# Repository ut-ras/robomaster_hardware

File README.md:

# Onboarding test branch

Use this branch to get accustomed to the git & github workflow, the current files are just a copy of the turret branch.

**Use `git clone  --recursive [Repository URL]` to clone our hardware repo**, as not doing so will not copy the files needed from the [RAS KiCAD Library](https://github.com/ut-ras/KiCad_Library.git)

It will put you on the `main` branch first, use `git switch onboard` to switch to this onboard branch.

To get the URL for this onboarding branch use the green `<> Code` button and copy the URL.

To confirm you are done with onboarding, clone this branch, edit this markdown file according to the directions below, and stage/commit/push the changes to this github repo:

Type your name and GitHub username here:

- Morris Lin : MorrisYLin
- Egan Wang:0 BaRho80
- Andrew Nguyen : AndrewNguy
- Sanjana Kishore : jujube6363
- Raeesa Karim : RaeesaKarim
- Nithin Reddy : NReddy101
- Sarthak Sarans : SarthakSarans

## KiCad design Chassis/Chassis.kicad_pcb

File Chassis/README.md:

# Chassis board

This project contains the chassis board, which routes power and CAN to the wheels from the PMM and the Dev Board, respectively.  
Also, a buck converter that drives the 19V power needed for the CV board. This is sent up the slip ring.

> _NOTE: 3D models will not work until someone figures out a clean way to use relative URLs for 3D models_

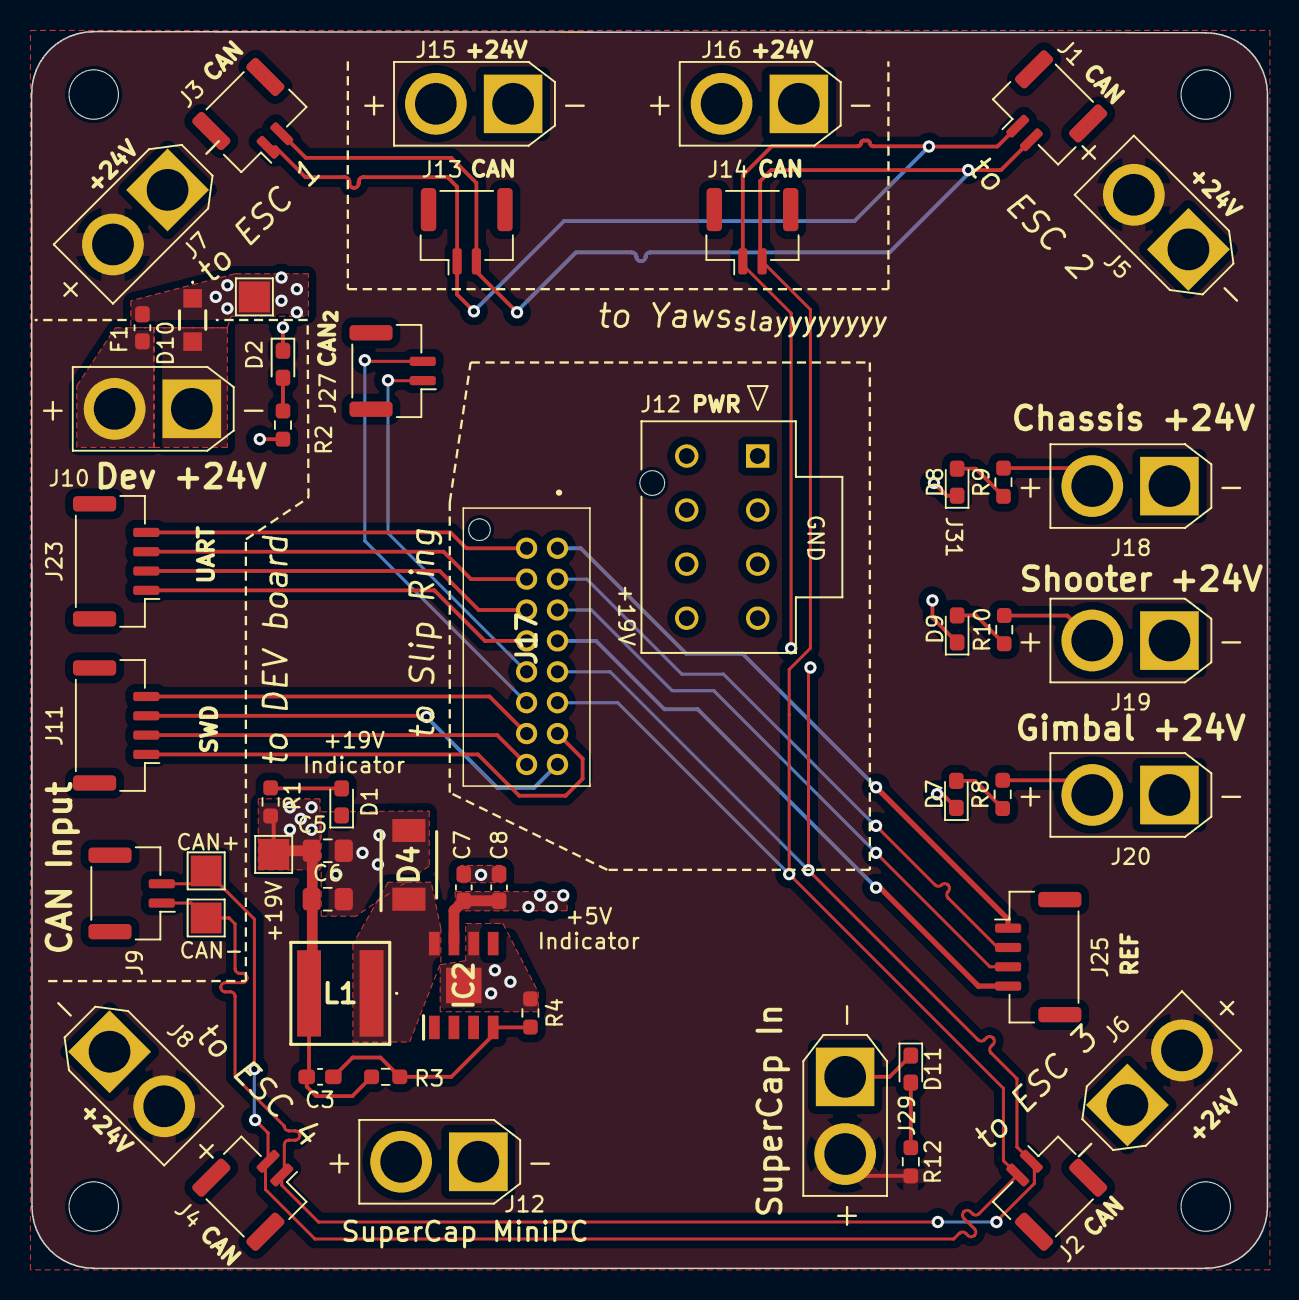
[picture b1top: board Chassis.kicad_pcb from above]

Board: 4 copper layers, 80.0 x 80.1 mm, 57 parts (0 on the bottom side), 35 nets.

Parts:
C3: 82pF; C_0603_1608Metric_Pad1.08x0.95mm_HandSolder
C5, C6: 22µF; C_0805_2012Metric_Pad1.18x1.45mm_HandSolder
C7, C8: 4.7µF; C_0603_1608Metric_Pad1.08x0.95mm_HandSolder
D1: 150060BS75000; LED_0603_1608Metric_Pad1.05x0.95mm_HandSolder
D2: 150060RS75000; LED_0603_1608Metric_Pad1.05x0.95mm_HandSolder
D4: SR54F-AU_R2_000A1; SODFL5336X110N
D7, D8, D9, D11: 150060YS75000; LED_0603_1608Metric_Pad1.05x0.95mm_HandSolder
D10: PTVS26VS1UR-QX; PTVS26VS1URQX
F1: 2.5A; Fuse_0603_1608Metric_Pad1.05x0.95mm_HandSolder
H1, H2, H3, H4: MountingHole; MountingHole_3.2mm_M3
IC2: RT6285GSP; SOIC127P600X175-9N
J1: FR_JST; JST_GH_BM02B-GHS-TBT_1x02-1MP_P1.25mm_Vertical
J2: BR_JST; JST_GH_BM02B-GHS-TBT_1x02-1MP_P1.25mm_Vertical
J3: FL_JST; JST_GH_BM02B-GHS-TBT_1x02-1MP_P1.25mm_Vertical
J4: BL_JST; JST_GH_BM02B-GHS-TBT_1x02-1MP_P1.25mm_Vertical
J5: FR_XT30; AMASS_XT30U-F_1x02_P5.0mm_Vertical
J6: BR_XT30; AMASS_XT30U-F_1x02_P5.0mm_Vertical
J7: FL_XT30; AMASS_XT30U-F_1x02_P5.0mm_Vertical
J8: BL_XT30; AMASS_XT30U-F_1x02_P5.0mm_Vertical
J9: IN_JST; JST_GH_BM02B-GHS-TBT_1x02-1MP_P1.25mm_Vertical
J10: IN_XT30; AMASS_XT30U-F_1x02_P5.0mm_Vertical
J11: SWD_IN; JST_GH_BM04B-GHS-TBT_1x04-1MP_P1.25mm_Vertical
J12, J29: SUPCAP_XT30; AMASS_XT30U-F_1x02_P5.0mm_Vertical
J13: GIM1_JST; JST_GH_BM02B-GHS-TBT_1x02-1MP_P1.25mm_Vertical
J14: GIM2_JST; JST_GH_BM02B-GHS-TBT_1x02-1MP_P1.25mm_Vertical
J15: GIM1_XT30; AMASS_XT30U-F_1x02_P5.0mm_Vertical
J16: GIM2_XT30; AMASS_XT30U-F_1x02_P5.0mm_Vertical
J17: 501645-1620; 5016451620
J18: CHA_XT30; AMASS_XT30U-F_1x02_P5.0mm_Vertical
J19: SHOO_XT30; AMASS_XT30U-F_1x02_P5.0mm_Vertical
J20: GIM_XT30; AMASS_XT30U-F_1x02_P5.0mm_Vertical
J23: UART_IN; JST_GH_BM04B-GHS-TBT_1x04-1MP_P1.25mm_Vertical
J25: REF_IN; JST_GH_BM04B-GHS-TBT_1x04-1MP_P1.25mm_Vertical
J27: CAN2_IN; JST_GH_BM02B-GHS-TBT_1x02-1MP_P1.25mm_Vertical
J31: Conn_01x08_Pin; CON_1722981108_MOL
L1: 10µH; MPLAL6060100
R1, R2, R8, R9, R10, R12: 1kΩ; R_0603_1608Metric_Pad0.98x0.95mm_HandSolder
R3: 100kΩ; R_0603_1608Metric_Pad0.98x0.95mm_HandSolder
R4: 6.8kΩ; R_0603_1608Metric_Pad0.98x0.95mm_HandSolder
TP1, TP2, TP3, TP4: TestPoint; TestPoint_Pad_2.0x2.0mm

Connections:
+3.3V: J11.4, J17.14
+3V3: J17.2, J23.4
+24V: C7.1, C8.1, D10.1 (K), F1.2, IC2.7 (VIN), R2.2, TP3.1
/24V -> 19V Buck Convertor/FB_{19}: C3.2, IC2.4 (FB), R3.2, R4.1
/24V -> 19V Buck Convertor/SW_{19}: D4.1 (K), IC2.8 (SW), L1.1
/+19V: C3.1, C5.1, C6.1, J31.8, L1.2, R1.1, R3.1, TP4.1
/+24V_Chassis: J18.2, J31.5, R9.2
/+24V_Gimbal: J15.2, J16.2, J20.2, J31.7, R8.2
/+24V_Shooter: J19.2, J31.6, R10.2
/+V_SuperCap: J5.2, J6.2, J7.2, J8.2, J29.2, R12.2
/CAN2+: J17.12, J27.2
/CAN2-: J17.10, J27.1
/CAN+: J1.2, J2.2, J3.2, J4.2, J9.2, J13.2, J14.2, J17.11, TP2.1
/CAN-: J1.1, J2.1, J3.1, J4.1, J9.1, J13.1, J14.1, J17.9, TP1.1
/Mini_PC: F1.1, J10.2, J12.2
/REF_CAN+: J17.5, J25.3
/REF_CAN-: J17.3, J25.2
/REF_PWR: J17.7, J25.4
/SWCLK: J11.2, J17.16
/SWDIO: J11.3, J17.15
/UART_RX: J17.4, J23.3
/UART_TX: J17.6, J23.2
GND: C5.2, C6.2, C7.2, C8.2, D2.1 (K), D4.2 (A), D10.2 (A), IC2.6 (GND_1), IC2.9 (GND_2), J10.1, J12.1, J31.4, R4.2
GND_CHASSIS: D8.1 (K), D11.1 (K), J5.1, J6.1, J7.1, J8.1, J18.1, J29.1, J31.1
GND_DEBUG: J11.1, J17.13
GND_GIMBAL: D7.1 (K), J15.1, J16.1, J20.1, J31.3
GND_REF: J17.1, J25.1
GND_SHOOTER: D9.1 (K), J19.1, J31.2
GND_UART: J17.8, J23.1
unnamed: D1.2 (A), R1.2
unnamed: D2.2 (A), R2.1
unnamed: D7.2 (A), R8.1
unnamed: D8.2 (A), R9.1
unnamed: D9.2 (A), R10.1
unnamed: D11.2 (A), R12.1

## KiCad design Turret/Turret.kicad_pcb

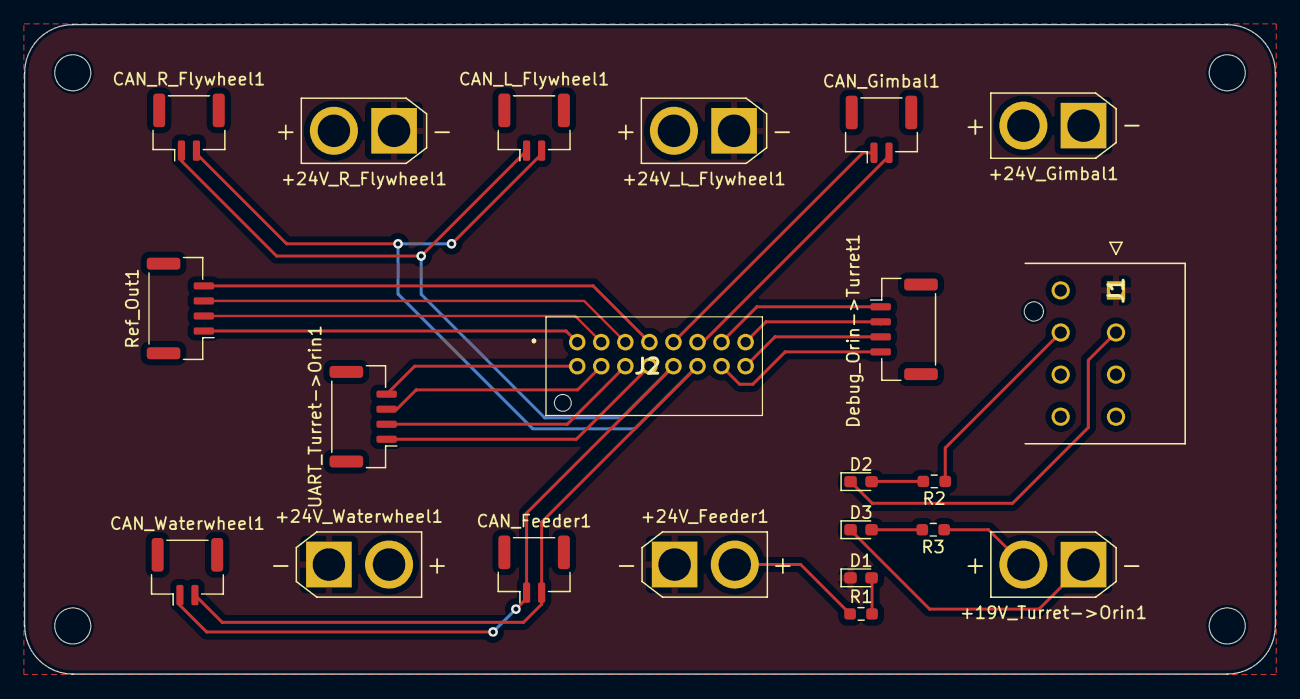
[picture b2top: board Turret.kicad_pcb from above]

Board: 2 copper layers, 104.0 x 54.0 mm, 26 parts (0 on the bottom side), 25 nets.

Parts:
+19V_Turret->Orin1, +24V_Feeder1, +24V_Gimbal1, +24V_L_Flywheel1, +24V_R_Flywheel1, +24V_Waterwheel1: Conn_01x02_Pin; AMASS_XT30U-F_1x02_P5.0mm_Vertical
CAN_Feeder1: Conn_01x02_Pin; JST_GH_BM02B-GHS-TBT_1x02-1MP_P1.25mm_Vertical
CAN_Gimbal1: Conn_01x02_Pin; JST_GH_BM02B-GHS-TBT_1x02-1MP_P1.25mm_Vertical
CAN_L_Flywheel1: Conn_01x02_Pin; JST_GH_BM02B-GHS-TBT_1x02-1MP_P1.25mm_Vertical
CAN_R_Flywheel1: Conn_01x02_Pin; JST_GH_BM02B-GHS-TBT_1x02-1MP_P1.25mm_Vertical
CAN_Waterwheel1: Conn_01x02_Pin; JST_GH_BM02B-GHS-TBT_1x02-1MP_P1.25mm_Vertical
D1, D2, D3: 150060YS75000; LED_0603_1608Metric_Pad1.05x0.95mm_HandSolder
Debug_Orin->Turret1: Conn_01x04_Pin; JST_GH_BM04B-GHS-TBT_1x04-1MP_P1.25mm_Vertical
H1, H2, H3, H4: MountingHole; MountingHole_3mm
J1: 172298-1108; 172298-YY08
J2: 501645-1620; 5016451620
R1, R2, R3: 1k; R_0603_1608Metric_Pad0.98x0.95mm_HandSolder
Ref_Out1: Conn_01x04_Pin; JST_GH_BM04B-GHS-TBT_1x04-1MP_P1.25mm_Vertical
UART_Turret->Orin1: Conn_01x04_Pin; JST_GH_BM04B-GHS-TBT_1x04-1MP_P1.25mm_Vertical

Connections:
/+19V: +19V_Turret->Orin1.2, J1.7, R3.1
/+24V_Gimbal: +24V_Gimbal1.2, J1.6, R2.1
/+24V_Shooter: +24V_Feeder1.2, +24V_L_Flywheel1.2, +24V_R_Flywheel1.2, +24V_Waterwheel1.2, J1.5, R1.1
/CANGim_H: CAN_Gimbal1.2, J2.11
/CANGim_L: CAN_Gimbal1.1, J2.9
/CANH: CAN_Feeder1.2, CAN_L_Flywheel1.2, CAN_R_Flywheel1.2, CAN_Waterwheel1.2, J2.12
/CANL: CAN_Feeder1.1, CAN_L_Flywheel1.1, CAN_R_Flywheel1.1, CAN_Waterwheel1.1, J2.10
/Gimbal_PWR_GND: +24V_Gimbal1.1, D2.1 (K), J1.2
/Orin_PWR_GND: +19V_Turret->Orin1.1, D3.1 (K), J1.3
/Ref_CAN+: J2.5, Ref_Out1.3
/Ref_CAN-: J2.3, Ref_Out1.2
/Ref_GND: J2.1, Ref_Out1.1
/Ref_PWR: J2.7, Ref_Out1.4
/SWD_3V3: Debug_Orin->Turret1.4, J2.14
/SWD_GND: Debug_Orin->Turret1.1, J2.13
/SWD_SWCLK: Debug_Orin->Turret1.3, J2.16
/SWD_SWDIO: Debug_Orin->Turret1.2, J2.15
/Shooter_PWR_GND: +24V_Feeder1.1, +24V_L_Flywheel1.1, +24V_R_Flywheel1.1, +24V_Waterwheel1.1, D1.1 (K), J1.1
/UART_3V3: J2.2, UART_Turret->Orin1.4
/UART_GND: J2.8, UART_Turret->Orin1.1
/UART_RX: J2.4, UART_Turret->Orin1.3
/UART_TX: J2.6, UART_Turret->Orin1.2
unnamed: D1.2 (A), R1.2
unnamed: D2.2 (A), R2.2
unnamed: D3.2 (A), R3.2

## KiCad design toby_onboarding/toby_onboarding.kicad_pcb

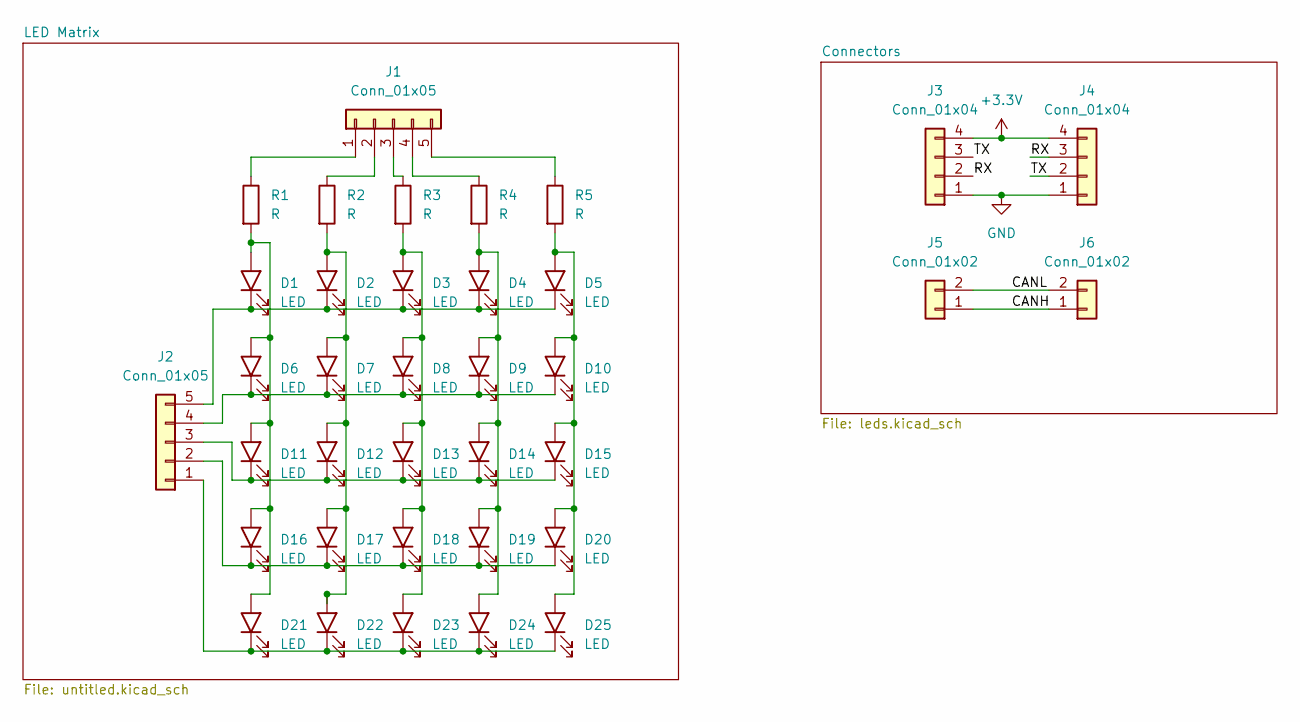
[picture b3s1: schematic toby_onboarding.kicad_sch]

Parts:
D1, D2, D3, D4, D5, D6, D7, D8, D9, D10, D11, D12, D13, D14, D15, D16, D17, D18, D19, D20, D21, D22, D23, D24, D25: LED; LED_D5.0mm
J1, J2: Conn_01x05; PinHeader_1x05_P2.54mm_Vertical
J3, J4: Conn_01x04; JST_GH_BM04B-GHS-TBT_1x04-1MP_P1.25mm_Vertical
J5, J6: Conn_01x02; JST_GH_BM02B-GHS-TBT_1x02-1MP_P1.25mm_Vertical
R1, R2, R3, R4, R5: R; R_Axial_DIN0207_L6.3mm_D2.5mm_P7.62mm_Horizontal

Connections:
+3.3V: J3.4, J4.4
/CANH: J5.1, J6.1
/CANL: J5.2, J6.2
/RX: J3.2, J4.3
/TX: J3.3, J4.2
GND: J3.1, J4.1
unnamed: D1.2 (A), D6.2 (A), D11.2 (A), D16.2 (A), D21.2 (A), R1.2
unnamed: D1.1 (K), D2.1 (K), D3.1 (K), D4.1 (K), D5.1 (K), J2.5
unnamed: D5.2 (A), D10.2 (A), D15.2 (A), D20.2 (A), D25.2 (A), R5.2
unnamed: D6.1 (K), D7.1 (K), D8.1 (K), D9.1 (K), D10.1 (K), J2.4
unnamed: D11.1 (K), D12.1 (K), D13.1 (K), D14.1 (K), D15.1 (K), J2.3
unnamed: D2.2 (A), D7.2 (A), D12.2 (A), D17.2 (A), D22.2 (A), R2.2
unnamed: D3.2 (A), D8.2 (A), D13.2 (A), D18.2 (A), D23.2 (A), R3.2
unnamed: D4.2 (A), D9.2 (A), D14.2 (A), D19.2 (A), D24.2 (A), R4.2
unnamed: D16.1 (K), D17.1 (K), D18.1 (K), D19.1 (K), D20.1 (K), J2.2
unnamed: D21.1 (K), D22.1 (K), D23.1 (K), D24.1 (K), D25.1 (K), J2.1
unnamed: J1.1, R1.1
unnamed: J1.2, R2.1
unnamed: J1.3, R3.1
unnamed: J1.4, R4.1
unnamed: J1.5, R5.1

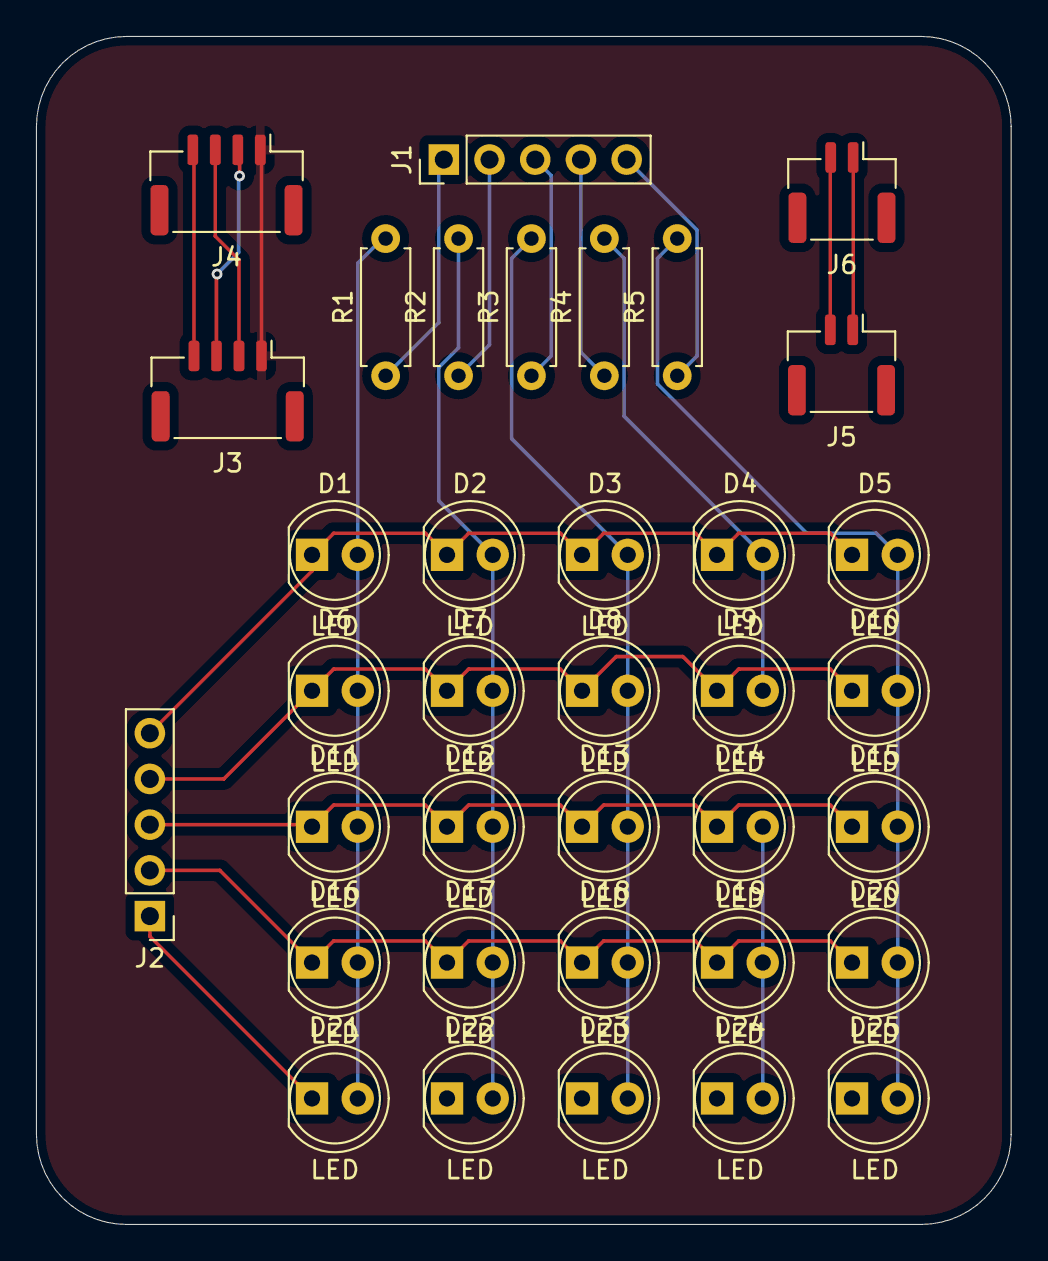
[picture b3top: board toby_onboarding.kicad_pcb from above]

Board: 2 copper layers, 54.2 x 66.0 mm, 36 parts (0 on the bottom side), 21 nets.

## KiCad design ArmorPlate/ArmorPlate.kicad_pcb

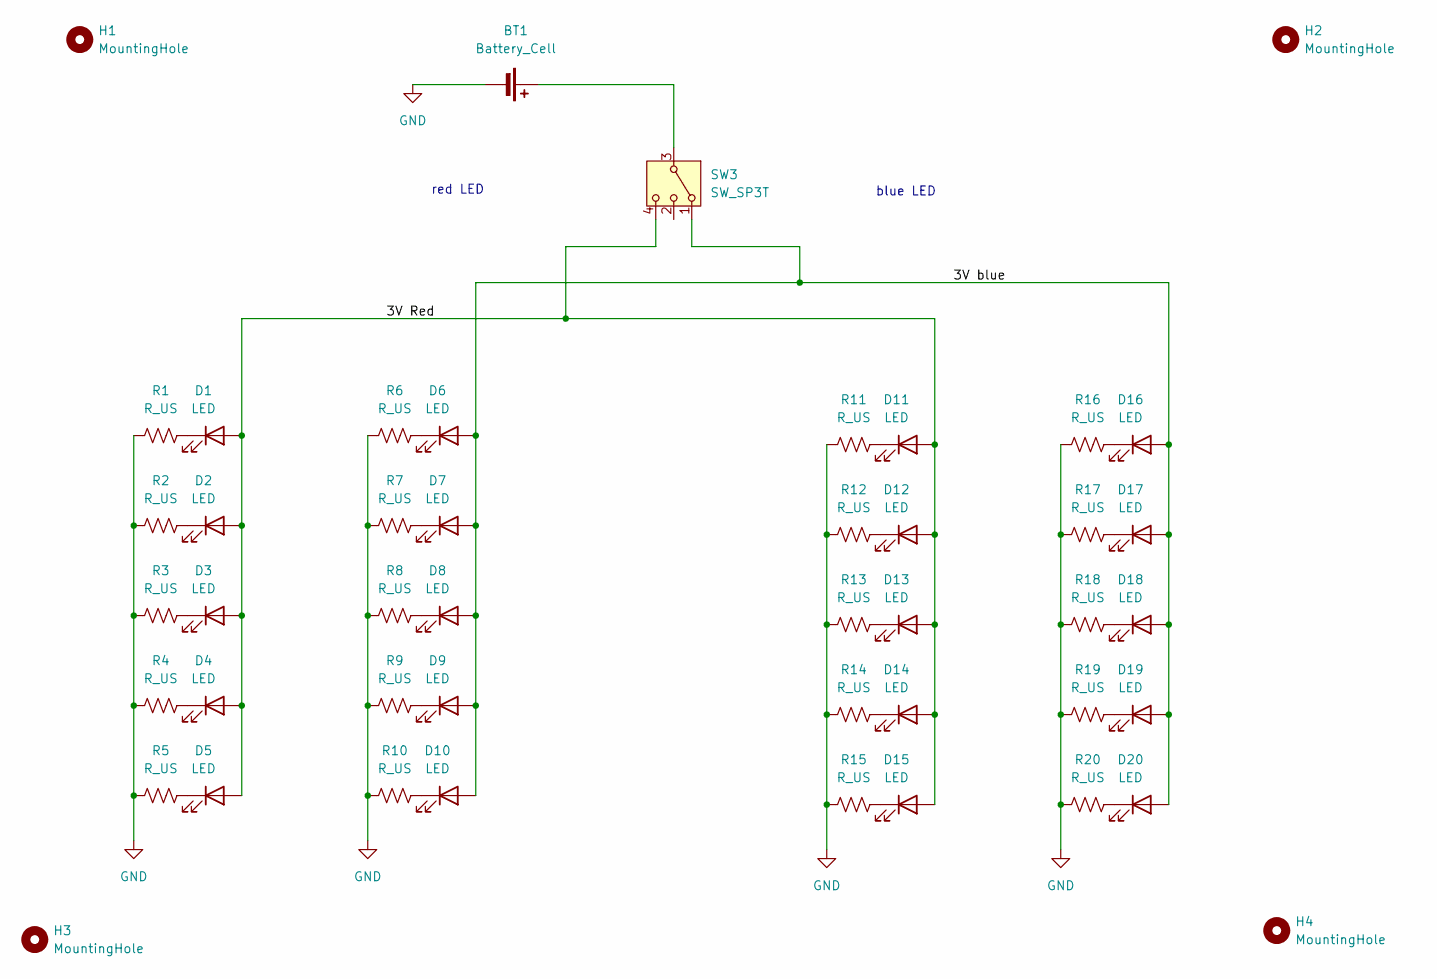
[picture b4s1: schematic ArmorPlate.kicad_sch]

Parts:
BT1: Battery_Cell; BatteryHolder_Keystone_2468_2xAAA; Mouser Part Number 613-MN1500-144
D1, D2, D3, D4, D5, D6, D7, D8, D9, D10, D11, D12, D13, D14, D15, D16, D17, D18, D19, D20: LED; LED_0603_1608Metric_Pad1.05x0.95mm_HandSolder; Mouser Part Number 710-150060SS75000
H1, H2, H3, H4: MountingHole; MountingHole_4.5mm
R1, R2, R3, R4, R5, R6, R7, R8, R9, R10, R11, R12, R13, R14, R15, R16, R17, R18, R19, R20: R_US; R_0603_1608Metric_Pad0.98x0.95mm_HandSolder; Mouser Part Number 71-WSLP25125L000FEA
SW3: SW_SP3T; EG1315AA

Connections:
/3V Red: D1.2 (A), D2.2 (A), D3.2 (A), D4.2 (A), D5.2 (A), D11.2 (A), D12.2 (A), D13.2 (A), D14.2 (A), D15.2 (A), SW3.4
/3V blue: D6.2 (A), D7.2 (A), D8.2 (A), D9.2 (A), D10.2 (A), D16.2 (A), D17.2 (A), D18.2 (A), D19.2 (A), D20.2 (A), SW3.1
GND: BT1.2 (-), R1.1, R2.1, R3.1, R4.1, R5.1, R6.1, R7.1, R8.1, R9.1, R10.1, R11.1, R12.1, R13.1, R14.1, R15.1, R16.1, R17.1, R18.1, R19.1, R20.1
unnamed: BT1.1 (+), SW3.3
unnamed: D1.1 (K), R1.2
unnamed: D2.1 (K), R2.2
unnamed: D3.1 (K), R3.2
unnamed: D4.1 (K), R4.2
unnamed: D5.1 (K), R5.2
unnamed: D6.1 (K), R6.2
unnamed: D7.1 (K), R7.2
unnamed: D8.1 (K), R8.2
unnamed: D9.1 (K), R9.2
unnamed: D10.1 (K), R10.2
unnamed: D11.1 (K), R11.2
unnamed: D12.1 (K), R12.2
unnamed: D13.1 (K), R13.2
unnamed: D14.1 (K), R14.2
unnamed: D15.1 (K), R15.2
unnamed: D16.1 (K), R16.2
unnamed: D17.1 (K), R17.2
unnamed: D18.1 (K), R18.2
unnamed: D19.1 (K), R19.2
unnamed: D20.1 (K), R20.2

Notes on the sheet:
blue LED
red LED

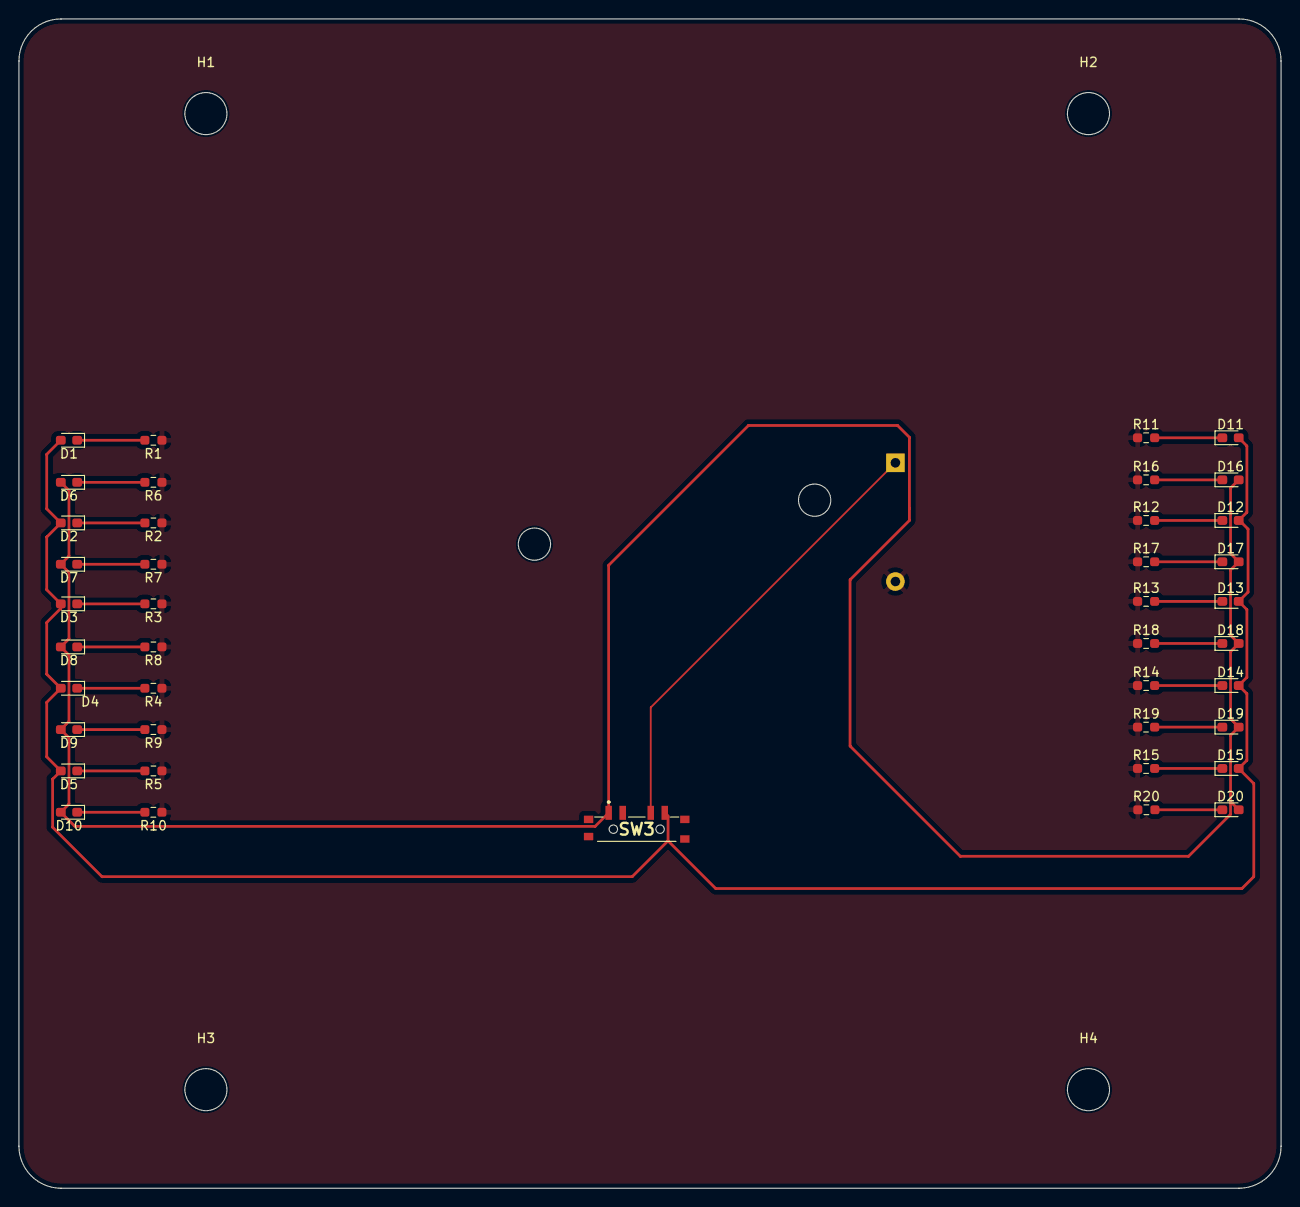
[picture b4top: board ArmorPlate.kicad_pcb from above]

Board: 2 copper layers, 135.0 x 125.1 mm, 46 parts (1 on the bottom side), 24 nets.

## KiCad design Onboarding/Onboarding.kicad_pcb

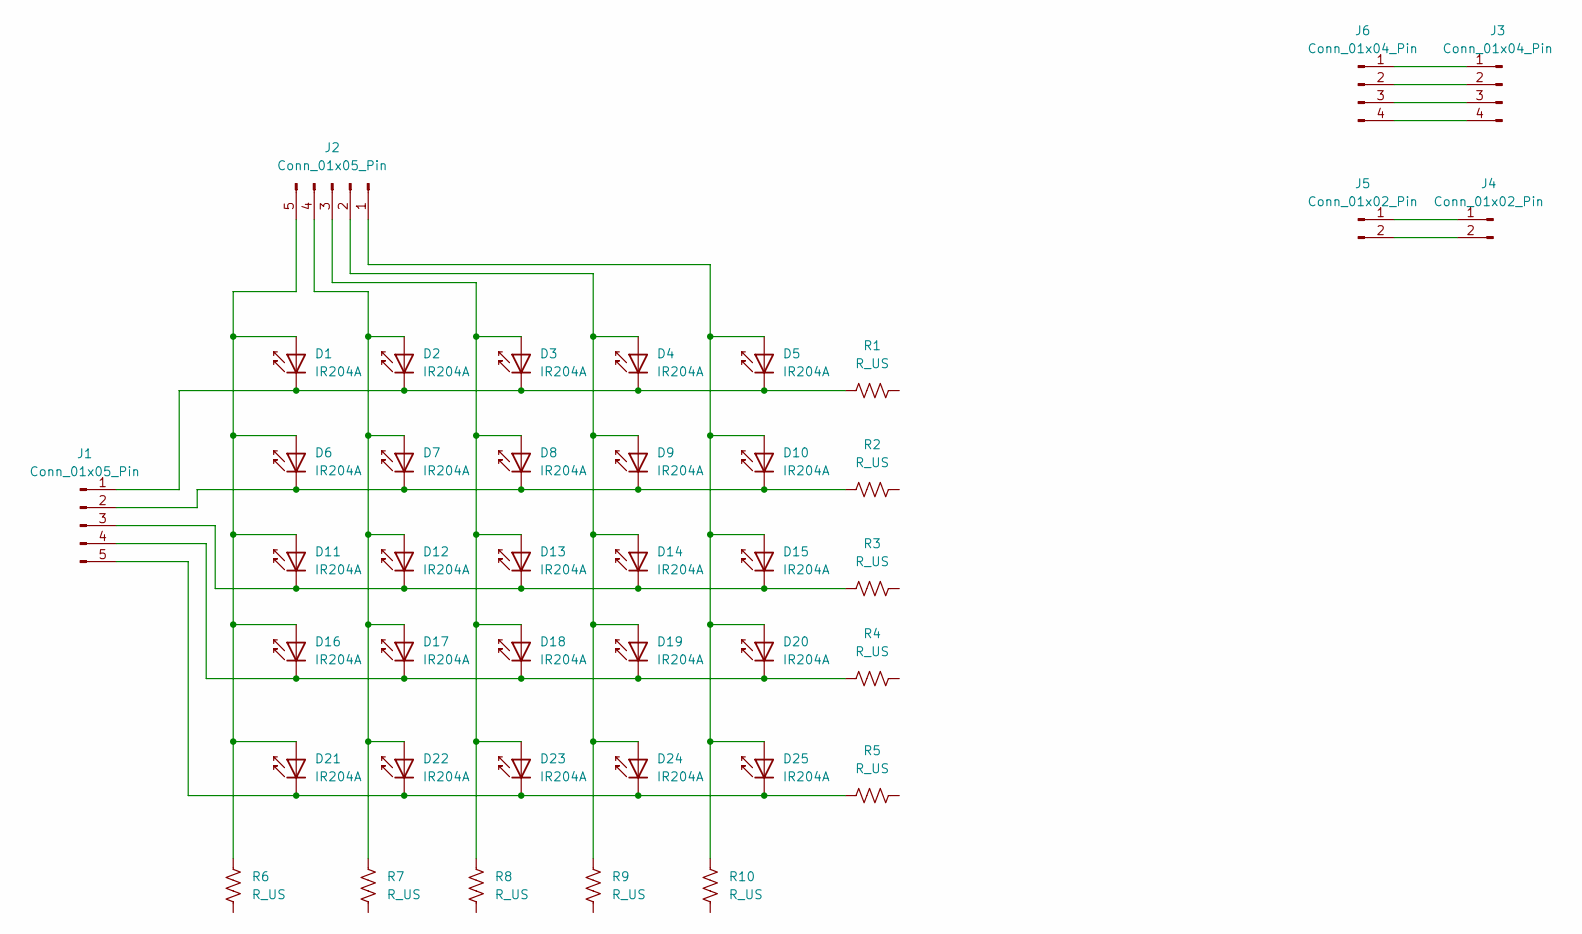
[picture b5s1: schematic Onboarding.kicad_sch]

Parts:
D1, D2, D3, D4, D5, D6, D7, D8, D9, D10, D11, D12, D13, D14, D15, D16, D17, D18, D19, D20, D21, D22, D23, D24, D25: IR204A; LED_D3.0mm_IRBlack
J1, J2: Conn_01x05_Pin; PinHeader_1x05_P2.54mm_Horizontal
J3, J6: Conn_01x04_Pin; PinHeader_1x04_P2.54mm_Horizontal
J4, J5: Conn_01x02_Pin; PinHeader_1x02_P2.54mm_Horizontal
R1, R2, R3, R4, R5, R6, R7, R8, R9, R10: R_US; R_Axial_DIN0207_L6.3mm_D2.5mm_P7.62mm_Horizontal

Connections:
unnamed: D1.2 (A), D6.2 (A), D11.2 (A), D16.2 (A), D21.2 (A), J2.5, R6.2
unnamed: D1.1 (K), D2.1 (K), D3.1 (K), D4.1 (K), D5.1 (K), J1.1, R1.2
unnamed: D5.2 (A), D10.2 (A), D15.2 (A), D20.2 (A), D25.2 (A), J2.1, R10.2
unnamed: D6.1 (K), D7.1 (K), D8.1 (K), D9.1 (K), D10.1 (K), J1.2, R2.2
unnamed: D11.1 (K), D12.1 (K), D13.1 (K), D14.1 (K), D15.1 (K), J1.3, R3.2
unnamed: D2.2 (A), D7.2 (A), D12.2 (A), D17.2 (A), D22.2 (A), J2.4, R7.2
unnamed: D3.2 (A), D8.2 (A), D13.2 (A), D18.2 (A), D23.2 (A), J2.3, R8.2
unnamed: D4.2 (A), D9.2 (A), D14.2 (A), D19.2 (A), D24.2 (A), J2.2, R9.2
unnamed: D16.1 (K), D17.1 (K), D18.1 (K), D19.1 (K), D20.1 (K), J1.4, R4.2
unnamed: D21.1 (K), D22.1 (K), D23.1 (K), D24.1 (K), D25.1 (K), J1.5, R5.2
unnamed: J3.1, J6.1
unnamed: J3.2, J6.2
unnamed: J3.3, J6.3
unnamed: J3.4, J6.4
unnamed: J4.1, J5.1
unnamed: J4.2, J5.2

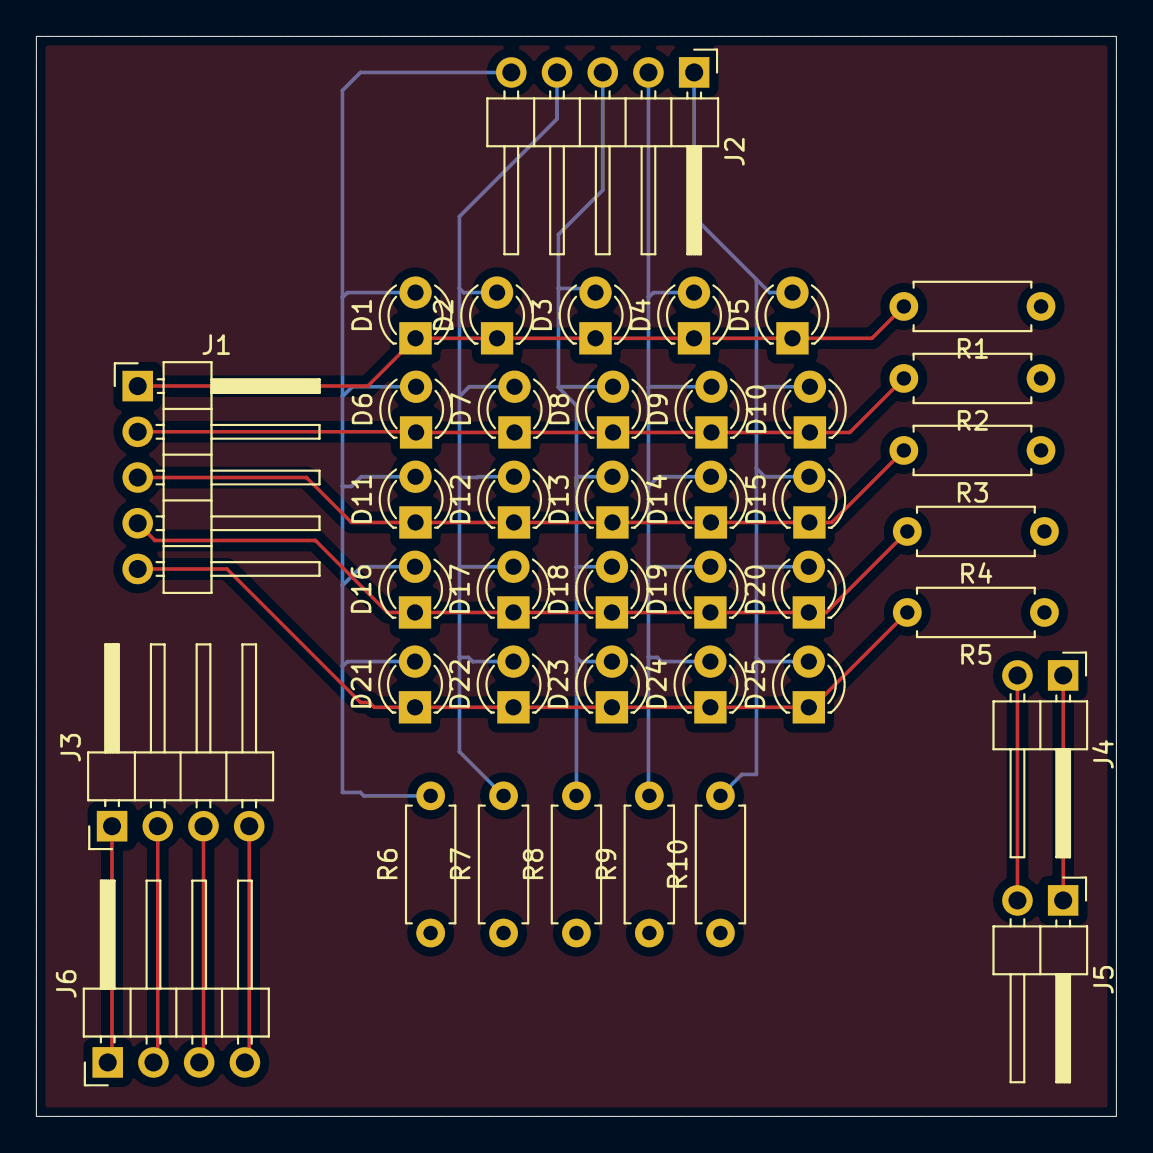
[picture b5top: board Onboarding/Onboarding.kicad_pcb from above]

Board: 2 copper layers, 60.0 x 60.0 mm, 41 parts (0 on the bottom side), 16 nets.

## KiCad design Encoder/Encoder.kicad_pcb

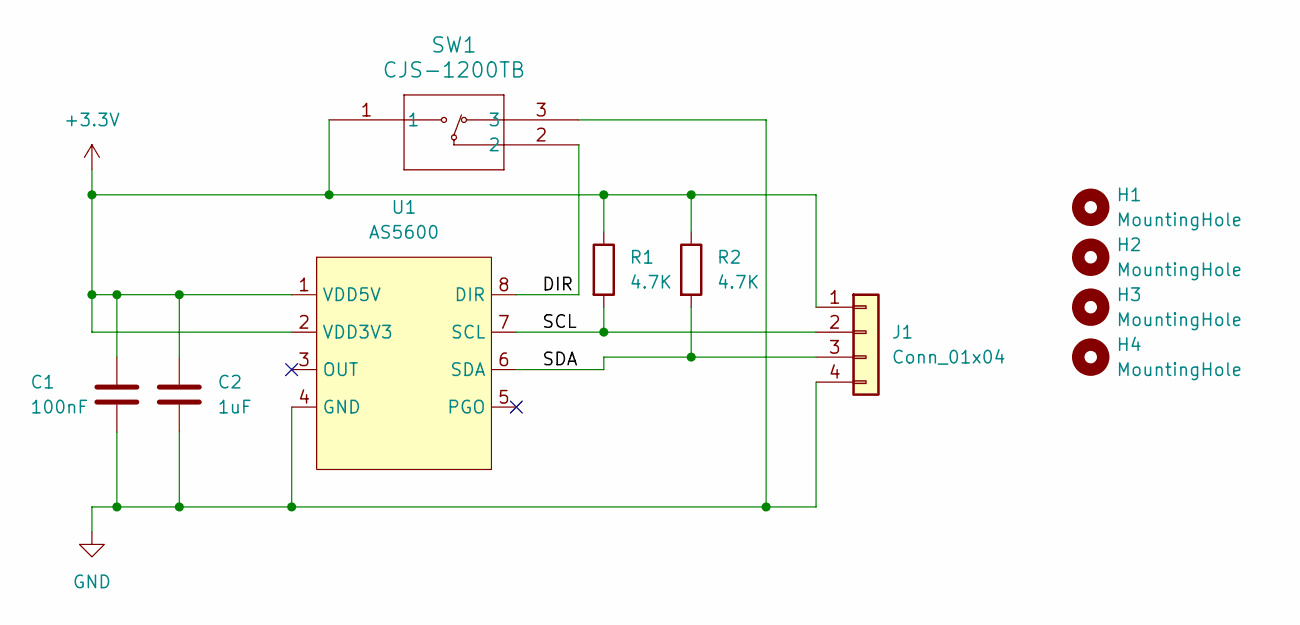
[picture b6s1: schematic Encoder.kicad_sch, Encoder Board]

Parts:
C1: 100nF; C_0603_1608Metric
C2: 1uF; C_0603_1608Metric
H1, H2, H3, H4: MountingHole; MountingHole_3.2mm_M3
J1: Conn_01x04; JST_GH_SM04B-GHS-TB_1x04-1MP_P1.25mm_Horizontal
R1, R2: 4.7K; R_0603_1608Metric
SW1: CJS-1200TB; CJS-1200B_NDC
U1: AS5600; SOIC-8_3.9x4.9mm_P1.27mm

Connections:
+3.3V: C1.1, C2.1, J1.1, R1.1, R2.1, SW1.1, U1.1 (VDD5V), U1.2 (VDD3V3)
/DIR: SW1.2, U1.8 (DIR)
/SCL: J1.2, R1.2, U1.7 (SCL)
/SDA: J1.3, R2.2, U1.6 (SDA)
GND: C1.2, C2.2, J1.4, SW1.3, U1.4 (GND)

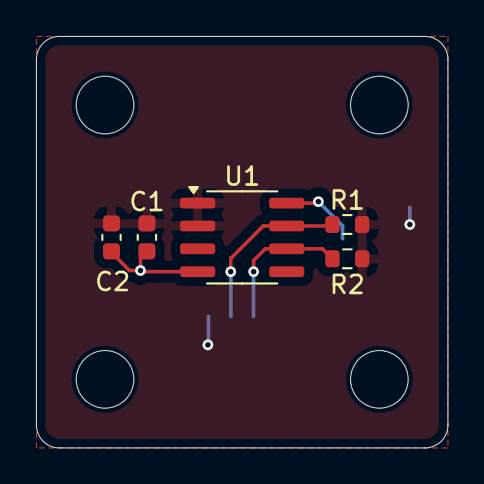
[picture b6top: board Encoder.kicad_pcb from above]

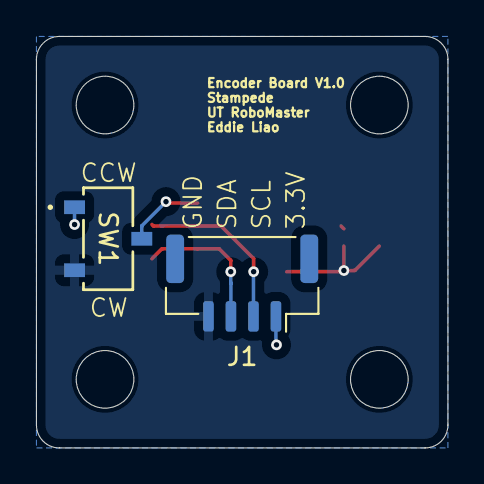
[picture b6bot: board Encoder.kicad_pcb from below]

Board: 2 copper layers, 22.9 x 22.9 mm, 11 parts (2 on the bottom side), 5 nets.

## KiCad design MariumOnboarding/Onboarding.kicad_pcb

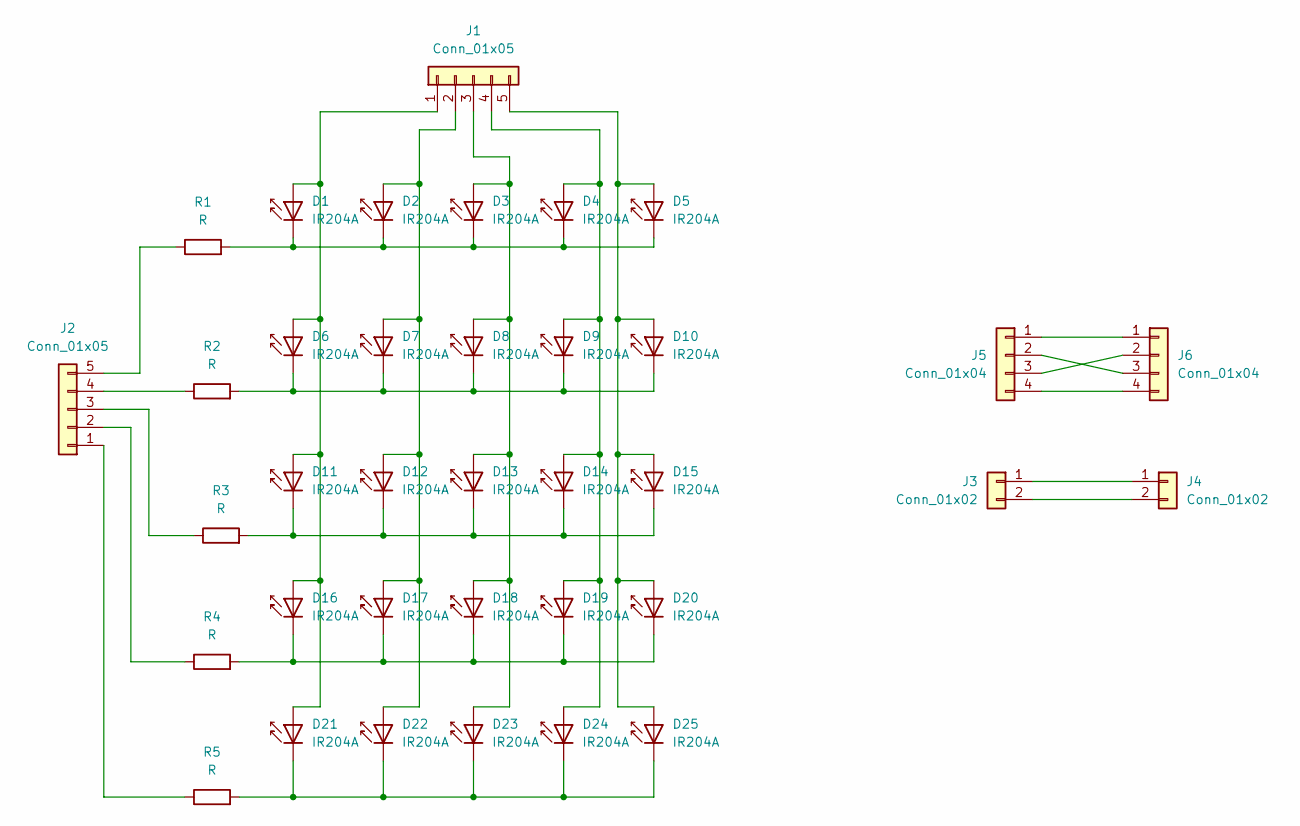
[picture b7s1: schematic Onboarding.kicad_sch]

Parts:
D1, D2, D3, D4, D5, D6, D7, D8, D9, D10, D11, D12, D13, D14, D15, D16, D17, D18, D19, D20, D21, D22, D23, D24, D25: IR204A; LED_D3.0mm_IRBlack
J1, J2: Conn_01x05; PinHeader_1x05_P2.54mm_Vertical
J3, J4: Conn_01x02; JST_GH_BM02B-GHS-TBT_1x02-1MP_P1.25mm_Vertical
J5, J6: Conn_01x04; JST_GH_BM04B-GHS-TBT_1x04-1MP_P1.25mm_Vertical
R1, R2, R3, R4, R5: R; R_Axial_DIN0207_L6.3mm_D2.5mm_P7.62mm_Horizontal

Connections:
unnamed: D1.2 (A), D6.2 (A), D11.2 (A), D16.2 (A), D21.2 (A), J1.1
unnamed: D1.1 (K), D2.1 (K), D3.1 (K), D4.1 (K), D5.1 (K), R1.2
unnamed: D5.2 (A), D10.2 (A), D15.2 (A), D20.2 (A), D25.2 (A), J1.5
unnamed: D6.1 (K), D7.1 (K), D8.1 (K), D9.1 (K), D10.1 (K), R2.2
unnamed: D11.1 (K), D12.1 (K), D13.1 (K), D14.1 (K), D15.1 (K), R3.2
unnamed: D2.2 (A), D7.2 (A), D12.2 (A), D17.2 (A), D22.2 (A), J1.2
unnamed: D3.2 (A), D8.2 (A), D13.2 (A), D18.2 (A), D23.2 (A), J1.3
unnamed: D4.2 (A), D9.2 (A), D14.2 (A), D19.2 (A), D24.2 (A), J1.4
unnamed: D16.1 (K), D17.1 (K), D18.1 (K), D19.1 (K), D20.1 (K), R4.2
unnamed: D21.1 (K), D22.1 (K), D23.1 (K), D24.1 (K), D25.1 (K), R5.2
unnamed: J2.1, R5.1
unnamed: J2.2, R4.1
unnamed: J2.3, R3.1
unnamed: J2.4, R2.1
unnamed: J2.5, R1.1
unnamed: J3.1, J4.1
unnamed: J3.2, J4.2
unnamed: J5.1, J6.1
unnamed: J5.2, J6.3
unnamed: J5.3, J6.2
unnamed: J5.4, J6.4

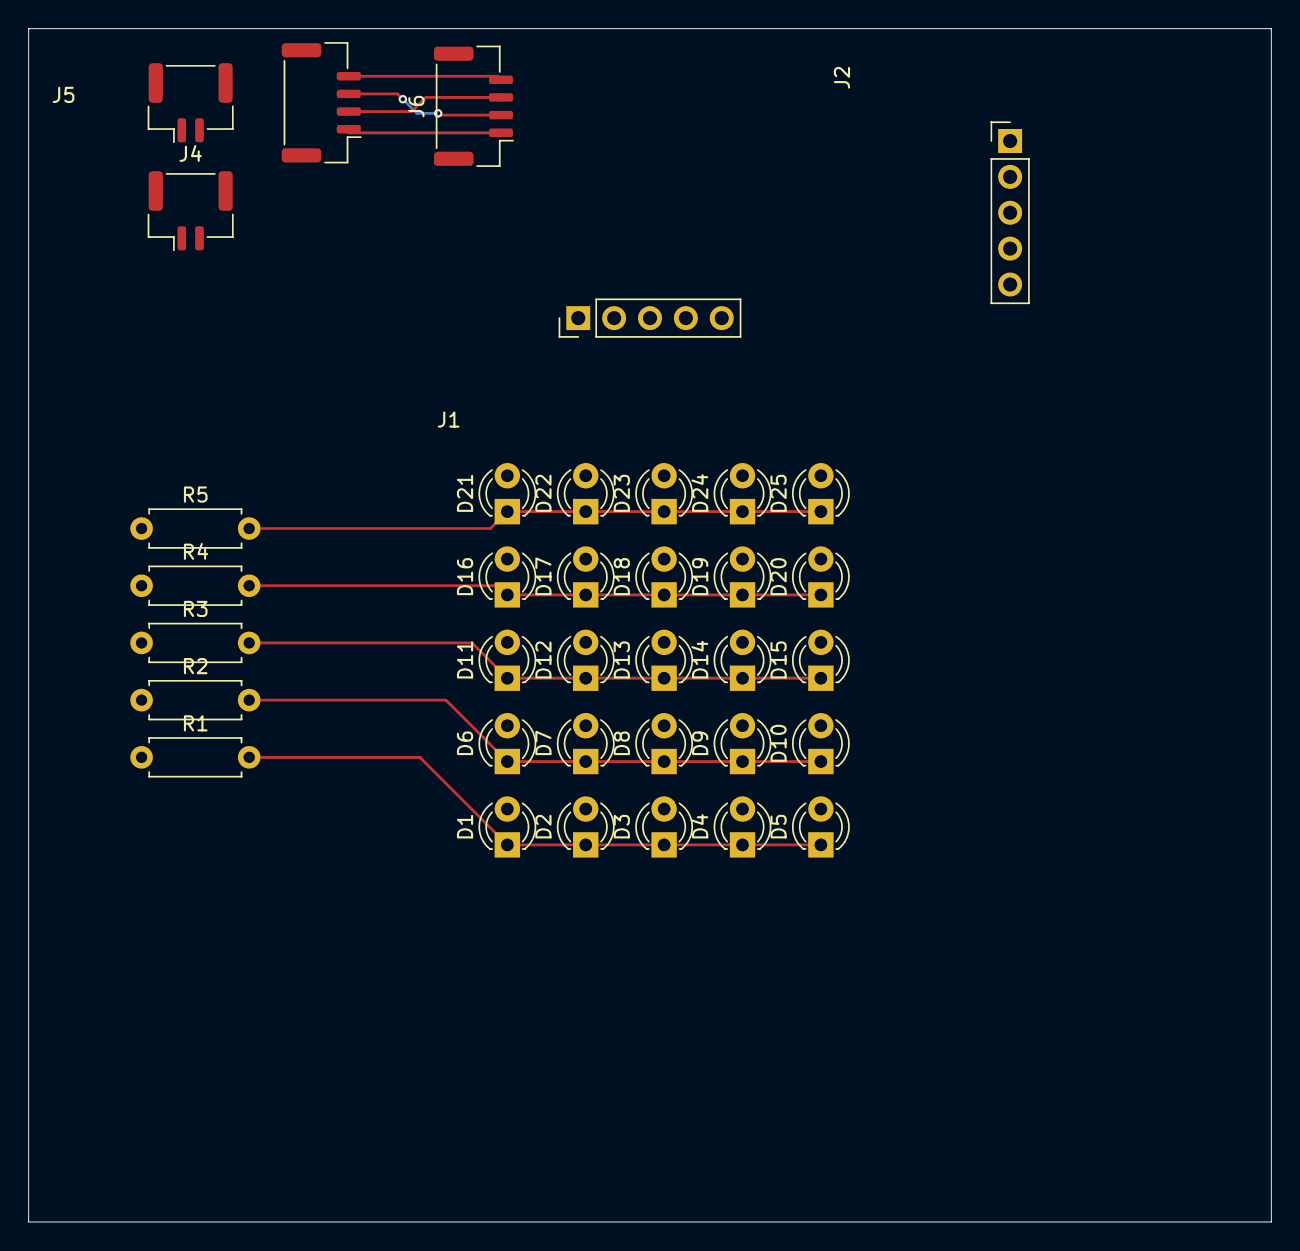
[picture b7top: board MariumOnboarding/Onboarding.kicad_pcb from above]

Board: 2 copper layers, 88.0 x 84.5 mm, 36 parts (0 on the bottom side), 21 nets.
